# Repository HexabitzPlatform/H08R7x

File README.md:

# H08R7x-Hardware
Hexabitz VL53L1 Time-of-Flight IR Sensor Module Hardware Design

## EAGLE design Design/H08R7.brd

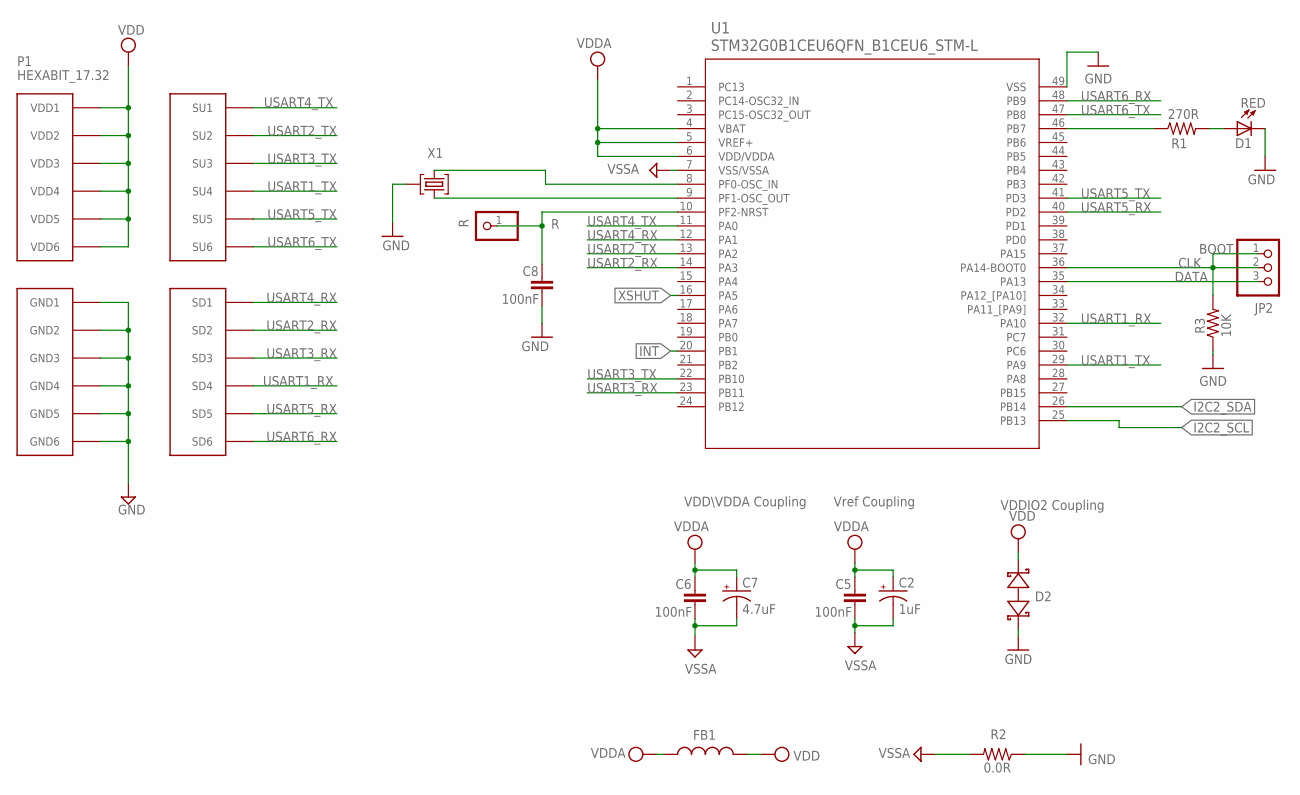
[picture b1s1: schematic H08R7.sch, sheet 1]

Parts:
C2: 1uF; C-0805-POL
C5, C6, C8: 100nF; C-0603
C7: 4.7uF; C-0805-POL
D1: RED; VLMS1300-GS08; MPN VLMS1300-GS08
D2: BOURNS_CDSOD323-T03SCBOURNS_CDSOD323-T03SC_0_0; BOURNS_CDSOD323-T03SC_0
FB1: FB-TDK_MMZ1608Y300B; MPN MMZ1608Y300B
JP2: PINHD-1X3; 1X03
P1: HEXABIT_17.32
R: R; 1X01
R1: 270R; R-0603
R2: 0.0R; R-0603; MPN RC0603JR-070RL
R3: 10K; R-0603
TRIMBLE-LOGO1: HEXA-LOGO
U1: STM32G0B1CEU6QFN_B1CEU6_STM-L; QFN_B1CEU6_STM-L
X1: XTALL_CSTCE8M00G52

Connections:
CLK: JP2.1, JP2.2, R3.2, U1.36 (PA14-BOOT0)
DATA: JP2.3, U1.35 (PA13)
GND: C8.2, D1.C, D2.1 (A), P1.PAD_PD7 (GND1), P1.PAD_PD8 (GND2), P1.PAD_PD9 (GND3), P1.PAD_PD10 (GND4), P1.PAD_PD11 (GND5), P1.PAD_PD12 (GND6), R2.1, R3.1, U1.49 (VSS), X1.P$2 (2); also elsewhere on the board
I2C2_SCL: U1.25 (PB13); also elsewhere on the board
I2C2_SDA: U1.26 (PB14); also elsewhere on the board
INT: U1.20 (PB1); also elsewhere on the board
unnamed: D1.A, R1.2
unnamed: C8.1, R.1, U1.10 (PF2-NRST)
unnamed: U1.9 (PF1-OSC_OUT), X1.P$1 (1)
unnamed: U1.8 (PF0-OSC_IN), X1.P$3 (3)
unnamed: R1.1, U1.46 (PB7)
USART1_RX: P1.PAD_PD4 (SD4), U1.32 (PA10)
USART1_TX: P1.PAD_PU4 (SU4), U1.29 (PA9)
USART2_RX: P1.PAD_PD2 (SD2), U1.14 (PA3)
USART2_TX: P1.PAD_PU2 (SU2), U1.13 (PA2)
USART3_RX: P1.PAD_PD3 (SD3), U1.23 (PB11)
USART3_TX: P1.PAD_PU3 (SU3), U1.22 (PB10)
USART4_RX: P1.PAD_PD1 (SD1), U1.12 (PA1)
USART4_TX: P1.PAD_PU1 (SU1), U1.11 (PA0)
USART5_RX: P1.PAD_PD5 (SD5), U1.40 (PD2)
USART5_TX: P1.PAD_PU5 (SU5), U1.41 (PD3)
USART6_RX: P1.PAD_PD6 (SD6), U1.48 (PB9)
USART6_TX: P1.PAD_PU6 (SU6), U1.47 (PB8)
VDD: D2.2 (C), FB1.2, P1.PAD_PU7 (VDD1), P1.PAD_PU8 (VDD2), P1.PAD_PU9 (VDD3), P1.PAD_PU10 (VDD4), P1.PAD_PU11 (VDD5), P1.PAD_PU12 (VDD6); also elsewhere on the board
VDDA: C2.1 (+), C5.1, C6.1, C7.1 (+), FB1.1, U1.4 (VBAT), U1.5 (VREF+), U1.6 (VDD/VDDA)
VSSA: C2.2 (-), C5.2, C6.2, C7.2 (-), R2.2, U1.7 (VSS/VSSA)
XSHUT: U1.16 (PA5); also elsewhere on the board

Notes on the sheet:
Vref Coupling
VDDIO2 Coupling
VDD\VDDA Coupling
BOOT

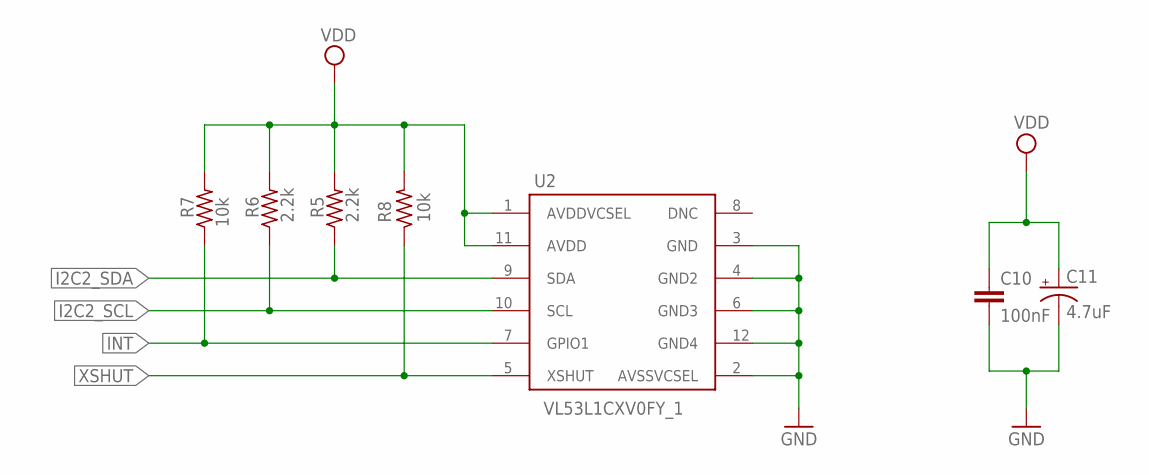
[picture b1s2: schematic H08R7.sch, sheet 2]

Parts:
C10: 100nF; C-0603
C11: 4.7uF; C-0805-POL
R5, R6: 2.2k; R-0603
R7, R8: 10k; R-0603
U2: VL53L1CXV0FY_1; VL53L1CXV0FY1

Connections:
GND: C10.2, C11.2 (-), U2.2 (AVSSVCSEL), U2.3 (GND), U2.4 (GND2), U2.6 (GND3), U2.12 (GND4); also elsewhere on the board
I2C2_SCL: R6.1, U2.10 (SCL); also elsewhere on the board
I2C2_SDA: R5.1, U2.9 (SDA); also elsewhere on the board
INT: R7.1, U2.7 (GPIO1); also elsewhere on the board
VDD: C10.1, C11.1 (+), R5.2, R6.2, R7.2, R8.2, U2.1 (AVDDVCSEL), U2.11 (AVDD); also elsewhere on the board
XSHUT: R8.1, U2.5 (XSHUT); also elsewhere on the board

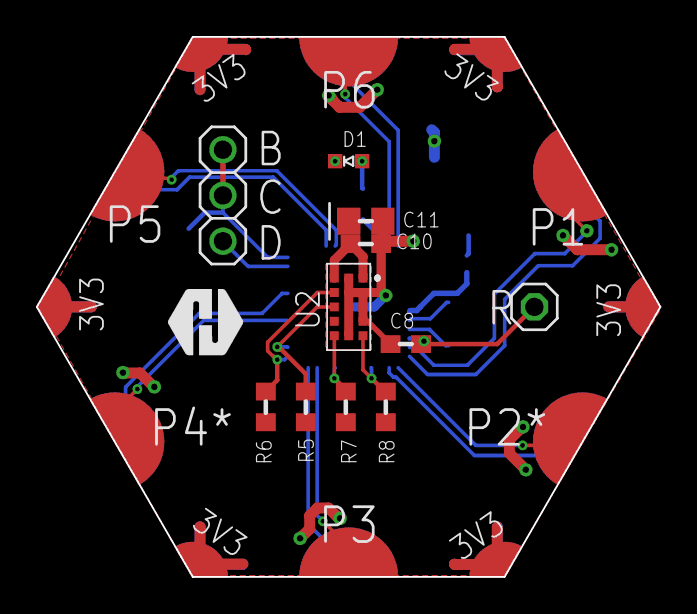
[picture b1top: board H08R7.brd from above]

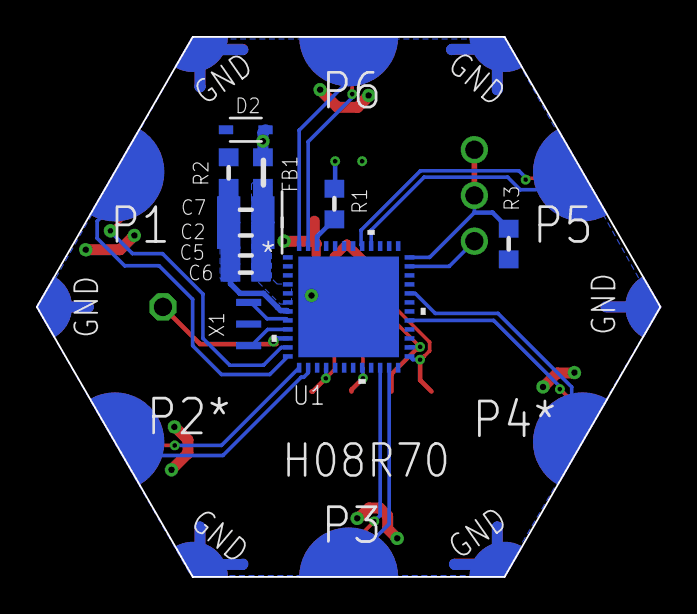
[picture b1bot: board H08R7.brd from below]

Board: 2 copper layers, 34.6 x 30.0 mm, 24 parts (11 on the bottom side), 27 nets.

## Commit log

2024-03-24 All Finish, Reviewed Version
2024-04-01 -Update the logo
2024-07-14 -Add TVS diode -Change the MCU to STM32G0B1CEU6 -Activate the thermal option for the polygon - fix the bom

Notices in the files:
parts and their libraries:
COPYRIGHT: Copyright (C) 2021 Ultra Librarian. All rights reserved.
